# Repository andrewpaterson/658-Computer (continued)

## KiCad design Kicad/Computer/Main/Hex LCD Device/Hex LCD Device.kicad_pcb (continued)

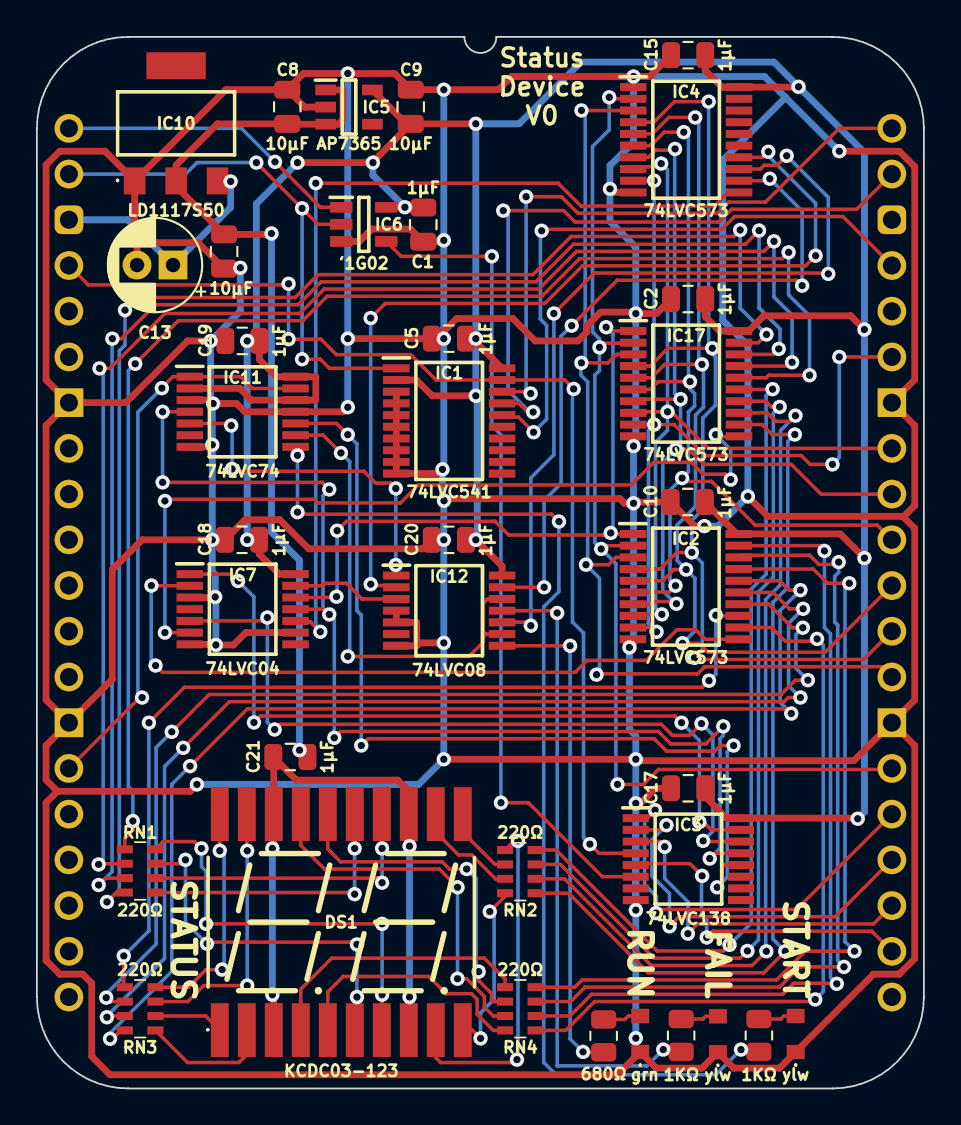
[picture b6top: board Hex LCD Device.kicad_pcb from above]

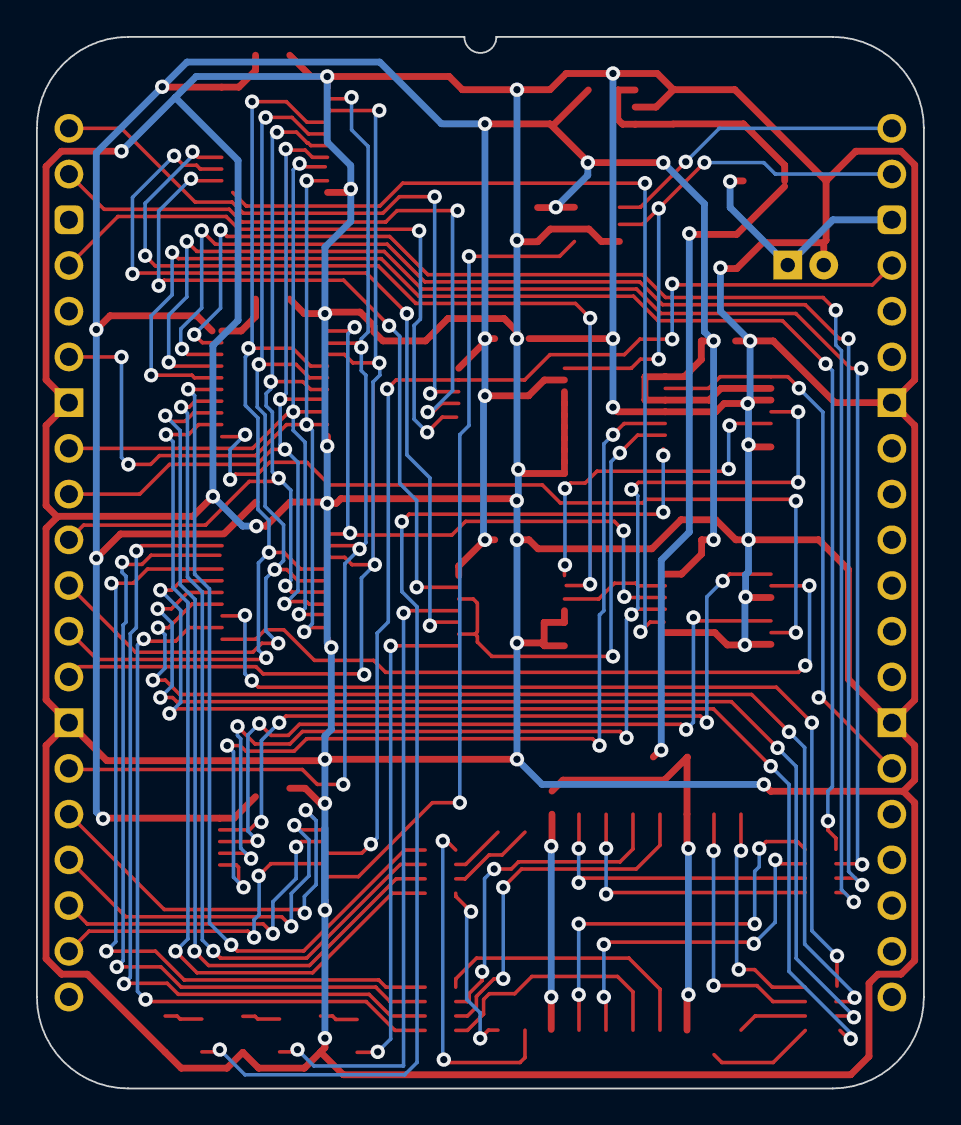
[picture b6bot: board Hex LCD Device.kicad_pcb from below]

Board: 2 copper layers, 49.3 x 58.4 mm, 40 parts (2 on the bottom side), 77 nets.

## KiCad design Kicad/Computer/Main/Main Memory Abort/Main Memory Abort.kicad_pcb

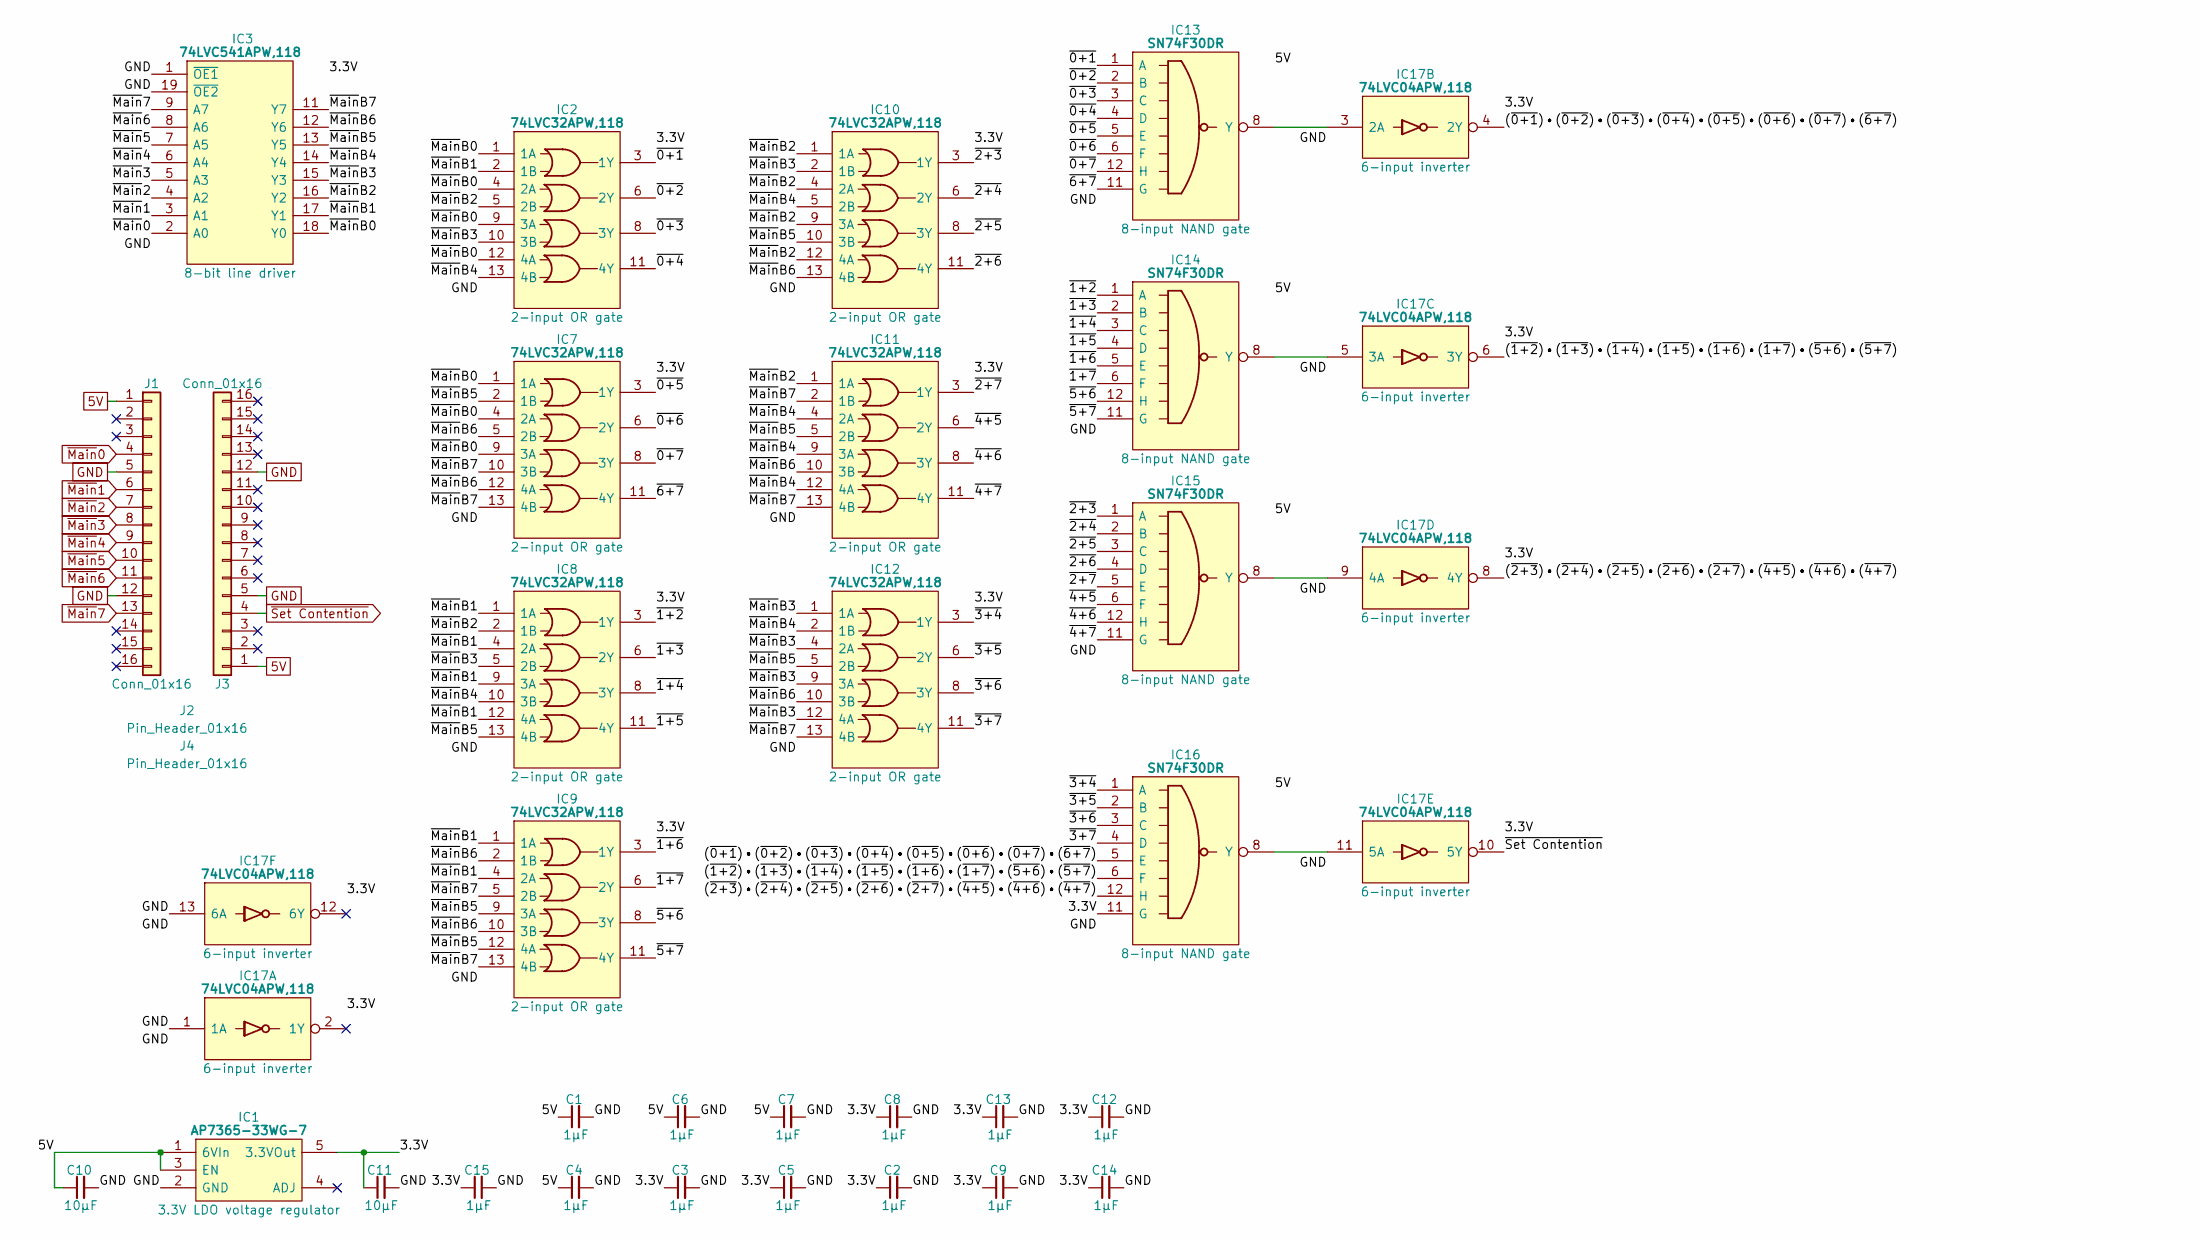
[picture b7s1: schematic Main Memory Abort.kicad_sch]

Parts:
C1, C2, C3, C4, C5, C6, C7, C8, C9, C12, C13, C14, C15: 1μF; C_0805
C10, C11: 10µF; C_0805
IC1: AP7365-33WG-7; SOT95P285X130-5N; Manufacturer_Part_Number AP7365-33WG-7; Mouser Part Number 621-AP7365-33WG-7
IC2, IC7, IC8, IC9, IC10, IC11, IC12: 74LVC32APW,118; SOP65P640X110-14N; Manufacturer_Part_Number 74LVC32APW,118; Mouser Part Number 771-74LVC32APW-T
IC3: 74LVC541APW,118; SOP65P640X110-20N; Mouser Part Number 771-74LVC541APW-T
IC13, IC14, IC15, IC16: SN74F30DR; SOIC127P600X175-14N; Manufacturer_Part_Number SN74F30DR; Mouser Part Number 595-SN74F30DR
IC17: 74LVC04APW,118; SOP65P640X110-14N; Manufacturer_Part_Number 74LVC04APW,118; Mouser Part Number 771-74LVC04APW-T
J1, J3: Conn_01x16; SIP_16_Pins
J2, J4: Pin_Header_01x16; PinHeader_1x16_P2.54mm_Vertical

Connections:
5V: C1.1, C4.1, C6.1, C7.1, C10.1, IC1.1 (6VIn), IC1.3 (EN), IC13.14 (5V), IC14.14 (5V), IC15.14 (5V), IC16.14 (5V), J1.1, J3.1
/3.3V: C2.1, C3.1, C5.1, C8.1, C9.1, C11.1, C12.1, C13.1, C14.1, C15.1, IC1.5 (3.3VOut), IC2.14 (3V), IC3.20 (3V), IC7.14 (3V), IC8.14 (3V), IC9.14 (3V), IC10.14 (3V), IC11.14 (3V), IC12.14 (3V), IC16.11 (G), IC17.14 (3V)
/(~0+1)•(~0+2)•(~0+3)•(~0+4)•(~0+5)•(~0+6)•(~0+7)•(~6+7): IC16.5 (E), IC17.4 (2Y)
/(~1+2)•(~1+3)•(~1+4)•(~1+5)•(~1+6)•(~1+7)•(~5+6)•(~5+7): IC16.6 (F), IC17.6 (3Y)
/(~2+3)•(~2+4)•(~2+5)•(~2+6)•(~2+7)•(~4+5)•(~4+6)•(~4+7): IC16.12 (H), IC17.8 (4Y)
/~0+1: IC2.3 (1Y), IC13.1 (A)
/~0+2: IC2.6 (2Y), IC13.2 (B)
/~0+3: IC2.8 (3Y), IC13.3 (C)
/~0+4: IC2.11 (4Y), IC13.4 (D)
/~0+5: IC7.3 (1Y), IC13.5 (E)
/~0+6: IC7.6 (2Y), IC13.6 (F)
/~0+7: IC7.8 (3Y), IC13.12 (H)
/~1+2: IC8.3 (1Y), IC14.1 (A)
/~1+3: IC8.6 (2Y), IC14.2 (B)
/~1+4: IC8.8 (3Y), IC14.3 (C)
/~1+5: IC8.11 (4Y), IC14.4 (D)
/~1+6: IC9.3 (1Y), IC14.5 (E)
/~1+7: IC9.6 (2Y), IC14.6 (F)
/~2+3: IC10.3 (1Y), IC15.1 (A)
/~2+4: IC10.6 (2Y), IC15.2 (B)
/~2+5: IC10.8 (3Y), IC15.3 (C)
/~2+6: IC10.11 (4Y), IC15.4 (D)
/~2+7: IC11.3 (1Y), IC15.5 (E)
/~3+4: IC12.3 (1Y), IC16.1 (A)
/~3+5: IC12.6 (2Y), IC16.2 (B)
/~3+6: IC12.8 (3Y), IC16.3 (C)
/~3+7: IC12.11 (4Y), IC16.4 (D)
/~4+5: IC11.6 (2Y), IC15.6 (F)
/~4+6: IC11.8 (3Y), IC15.12 (H)
/~4+7: IC11.11 (4Y), IC15.11 (G)
/~5+6: IC9.8 (3Y), IC14.12 (H)
/~5+7: IC9.11 (4Y), IC14.11 (G)
/~6+7: IC7.11 (4Y), IC13.11 (G)
/~MainB0: IC2.1 (1A), IC2.4 (2A), IC2.9 (3A), IC2.12 (4A), IC3.18 (Y0), IC7.1 (1A), IC7.4 (2A), IC7.9 (3A)
/~MainB1: IC2.2 (1B), IC3.17 (Y1), IC8.1 (1A), IC8.4 (2A), IC8.9 (3A), IC8.12 (4A), IC9.1 (1A), IC9.4 (2A)
/~MainB2: IC2.5 (2B), IC3.16 (Y2), IC8.2 (1B), IC10.1 (1A), IC10.4 (2A), IC10.9 (3A), IC10.12 (4A), IC11.1 (1A)
/~MainB3: IC2.10 (3B), IC3.15 (Y3), IC8.5 (2B), IC10.2 (1B), IC12.1 (1A), IC12.4 (2A), IC12.9 (3A), IC12.12 (4A)
/~MainB4: IC2.13 (4B), IC3.14 (Y4), IC8.10 (3B), IC10.5 (2B), IC11.4 (2A), IC11.9 (3A), IC11.12 (4A), IC12.2 (1B)
/~MainB5: IC3.13 (Y5), IC7.2 (1B), IC8.13 (4B), IC9.9 (3A), IC9.12 (4A), IC10.10 (3B), IC11.5 (2B), IC12.5 (2B)
/~MainB6: IC3.12 (Y6), IC7.5 (2B), IC7.12 (4A), IC9.2 (1B), IC9.10 (3B), IC10.13 (4B), IC11.10 (3B), IC12.10 (3B)
/~MainB7: IC3.11 (Y7), IC7.10 (3B), IC7.13 (4B), IC9.5 (2B), IC9.13 (4B), IC11.2 (1B), IC11.13 (4B), IC12.13 (4B)
GND: C1.2, C2.2, C3.2, C4.2, C5.2, C6.2, C7.2, C8.2, C9.2, C10.2, C11.2, C12.2, C13.2, C14.2, C15.2, IC1.2 (GND), IC2.7 (GND), IC3.1 (~OE1), IC3.10 (GND), IC3.19 (~OE2), IC7.7 (GND), IC8.7 (GND), IC9.7 (GND), IC10.7 (GND), IC11.7 (GND), IC12.7 (GND), IC13.7 (GND), IC14.7 (GND), IC15.7 (GND), IC16.7 (GND), IC17.1 (1A), IC17.7 (GND), IC17.13 (6A), J1.5, J1.12, J3.5, J3.12
unnamed: IC13.8 (Y), IC17.3 (2A)
unnamed: IC14.8 (Y), IC17.5 (3A)
unnamed: IC15.8 (Y), IC17.9 (4A)
unnamed: IC16.8 (Y), IC17.11 (5A)
~Main0: IC3.2 (A0), J1.4
~Main1: IC3.3 (A1), J1.6
~Main2: IC3.4 (A2), J1.7
~Main3: IC3.5 (A3), J1.8
~Main4: IC3.6 (A4), J1.9
~Main5: IC3.7 (A5), J1.10
~Main6: IC3.8 (A6), J1.11
~Main7: IC3.9 (A7), J1.13
~Set Contention: IC17.10 (5Y), J3.4

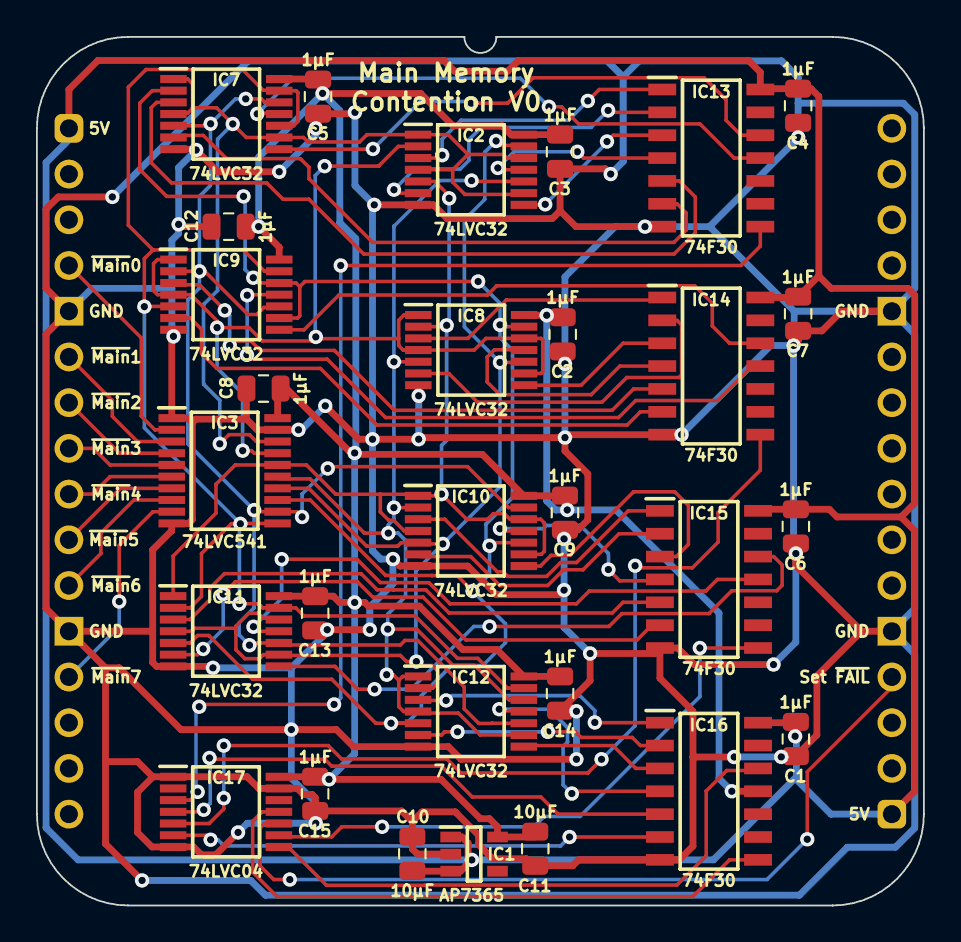
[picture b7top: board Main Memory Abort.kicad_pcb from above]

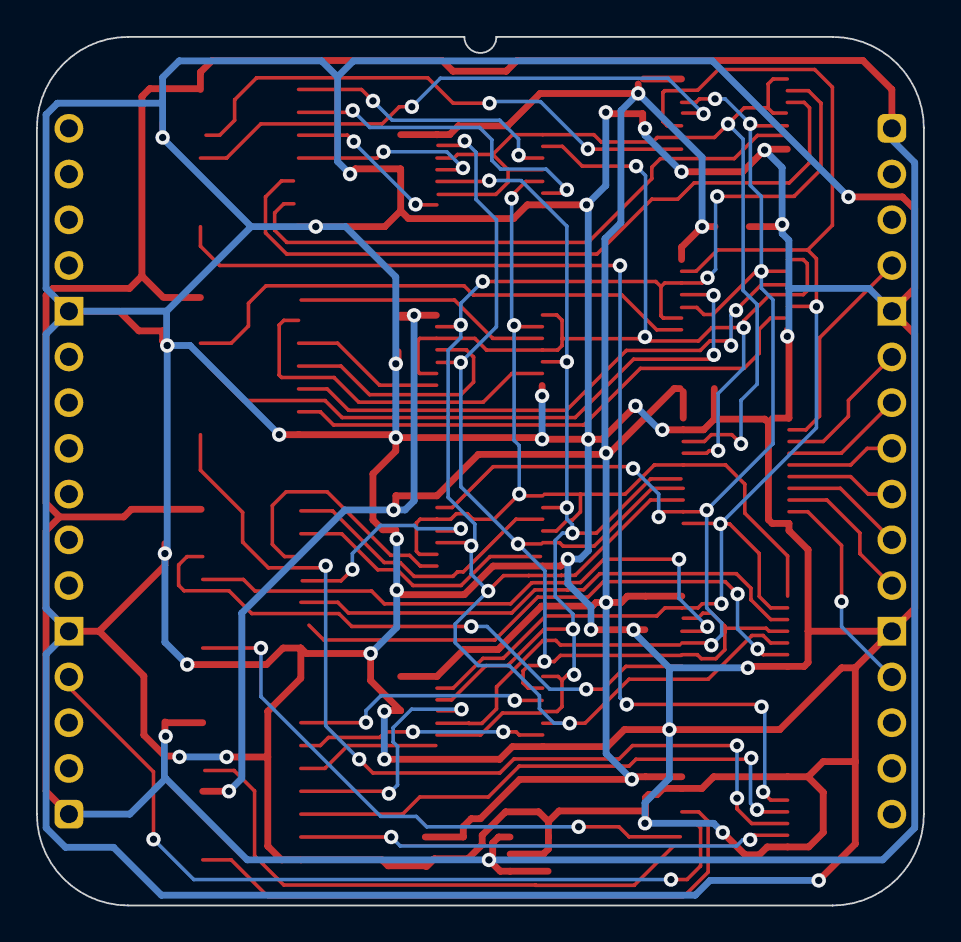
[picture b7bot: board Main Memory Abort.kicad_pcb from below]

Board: 2 copper layers, 49.3 x 48.3 mm, 33 parts (2 on the bottom side), 55 nets.

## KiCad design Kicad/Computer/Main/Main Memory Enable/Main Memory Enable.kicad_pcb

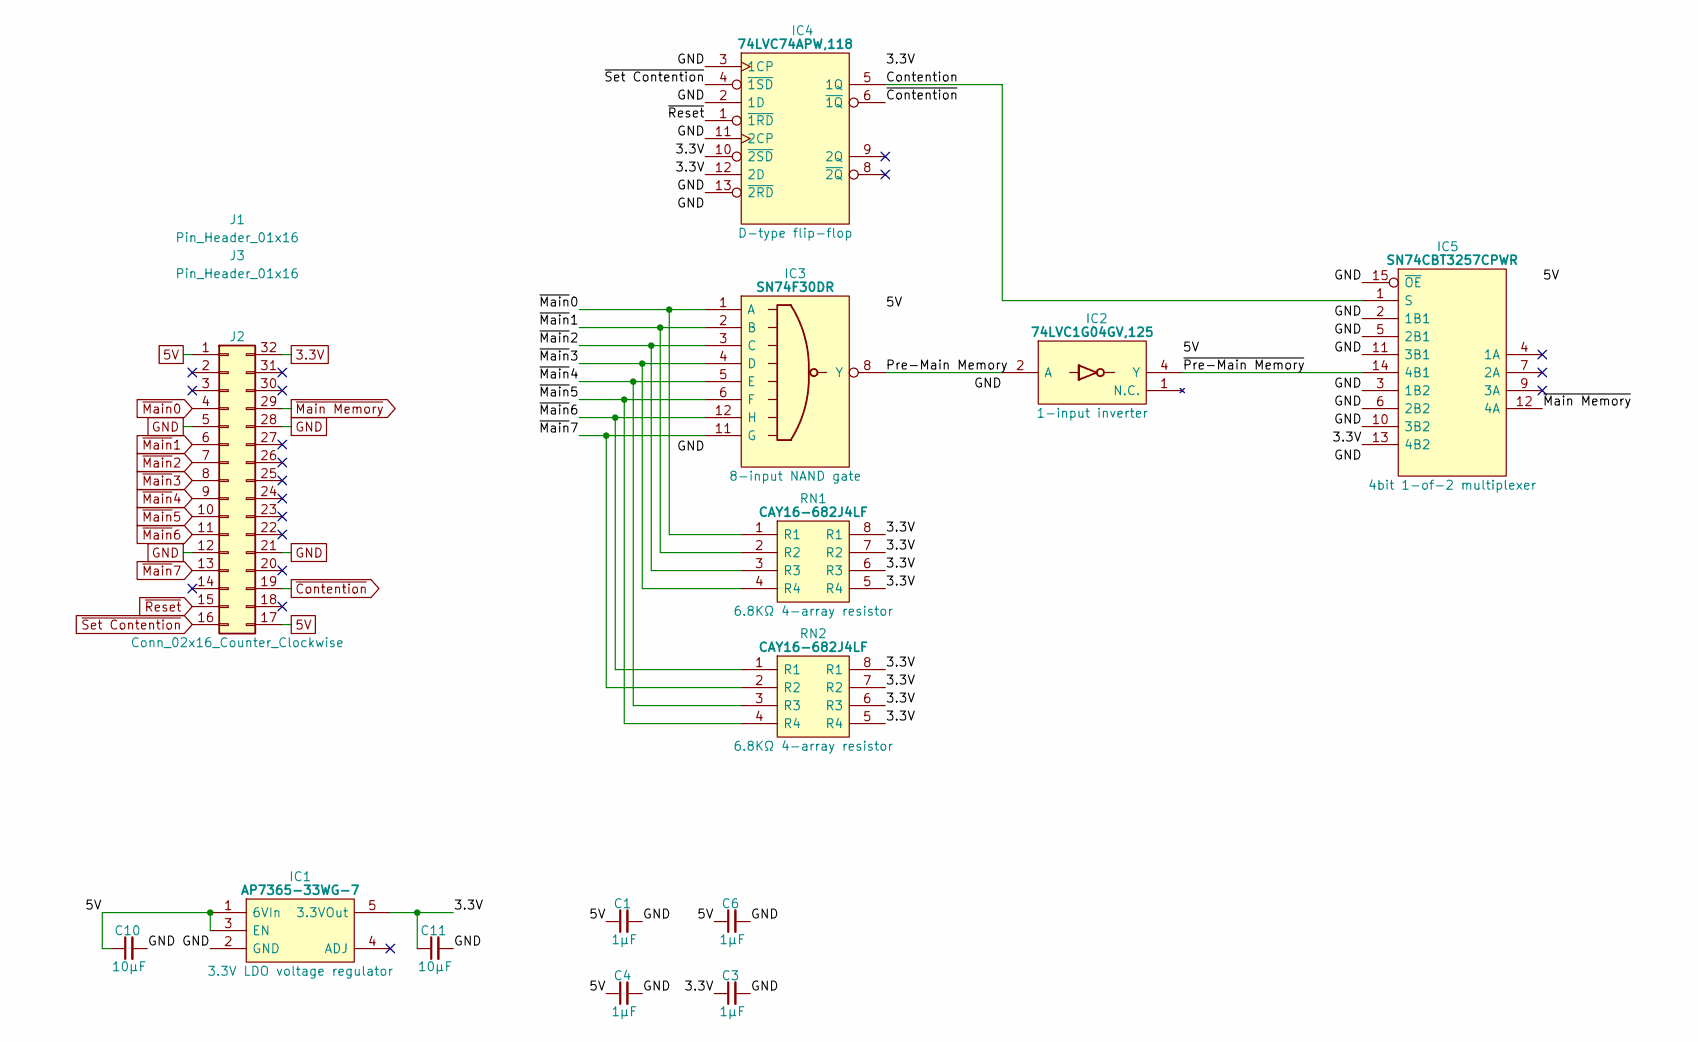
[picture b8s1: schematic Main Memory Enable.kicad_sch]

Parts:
C1, C3, C4, C6: 1μF; C_0805
C10, C11: 10µF; C_0805
IC1: AP7365-33WG-7; SOT95P285X130-5N; Manufacturer_Part_Number AP7365-33WG-7; Mouser Part Number 621-AP7365-33WG-7
IC2: 74LVC1G04GV,125; SOT95P275X110-5N; Manufacturer_Part_Number 74LVC1G04GV,125; Mouser Part Number 771-74LVC1G04GV
IC3: SN74F30DR; SOIC127P600X175-14N; Manufacturer_Part_Number SN74F30DR; Mouser Part Number 595-SN74F30DR
IC4: 74LVC74APW,118; SOP65P640X110-14N; Mouser Part Number 771-74LVC74APW-T
IC5: SN74CBT3257CPWR; SOP65P640X120-16N; Manufacturer_Part_Number SN74CBT3257CPWR; Mouser Part Number 595-SN74CBT3257CPWR
J1, J3: Pin_Header_01x16; PinHeader_1x16_P2.54mm_Vertical
J2: Conn_02x16_Counter_Clockwise; DIP-32_Board_W15.24mm
RN1, RN2: CAY16-682J4LF; CAY16-J4

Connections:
3.3V: C3.1, C11.1, IC1.5 (3.3VOut), IC4.10 (~2SD), IC4.12 (2D), IC4.14 (3V), IC5.13 (4B2), J2.32, RN1.5 (R4), RN1.6 (R3), RN1.7 (R2), RN1.8 (R1), RN2.5 (R4), RN2.6 (R3), RN2.7 (R2), RN2.8 (R1)
5V: C1.1, C4.1, C6.1, C10.1, IC1.1 (6VIn), IC1.3 (EN), IC2.5 (3V), IC3.14 (5V), IC5.16 (5V), J2.1, J2.17
/Contention: IC4.5 (1Q), IC5.1 (S)
/Pre-Main Memory: IC2.2 (A), IC3.8 (Y)
/~Pre-Main Memory: IC2.4 (Y), IC5.14 (4B1)
GND: C1.2, C3.2, C4.2, C6.2, C10.2, C11.2, IC1.2 (GND), IC2.3 (GND), IC3.7 (GND), IC4.2 (1D), IC4.3 (1CP), IC4.7 (GND), IC4.11 (2CP), IC4.13 (~2RD), IC5.2 (1B1), IC5.3 (1B2), IC5.5 (2B1), IC5.6 (2B2), IC5.8 (GND), IC5.10 (3B2), IC5.11 (3B1), IC5.15 (~OE), J2.5, J2.12, J2.21, J2.28
~Contention: IC4.6 (~1Q), J2.19
~Main Memory: IC5.12 (4A), J2.29
~Main0: IC3.1 (A), J2.4, RN1.1 (R1)
~Main1: IC3.2 (B), J2.6, RN1.2 (R2)
~Main2: IC3.3 (C), J2.7, RN1.3 (R3)
~Main3: IC3.4 (D), J2.8, RN1.4 (R4)
~Main4: IC3.5 (E), J2.9, RN2.3 (R3)
~Main5: IC3.6 (F), J2.10, RN2.4 (R4)
~Main6: IC3.12 (H), J2.11, RN2.1 (R1)
~Main7: IC3.11 (G), J2.13, RN2.2 (R2)
~Reset: IC4.1 (~1RD), J2.15
~Set Contention: IC4.4 (~1SD), J2.16

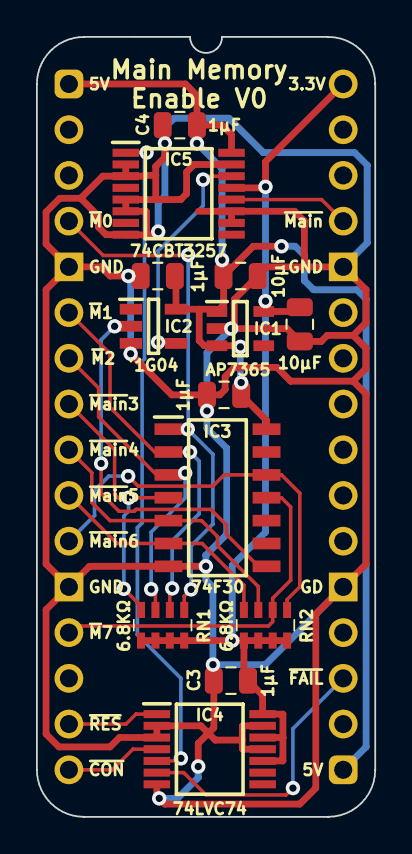
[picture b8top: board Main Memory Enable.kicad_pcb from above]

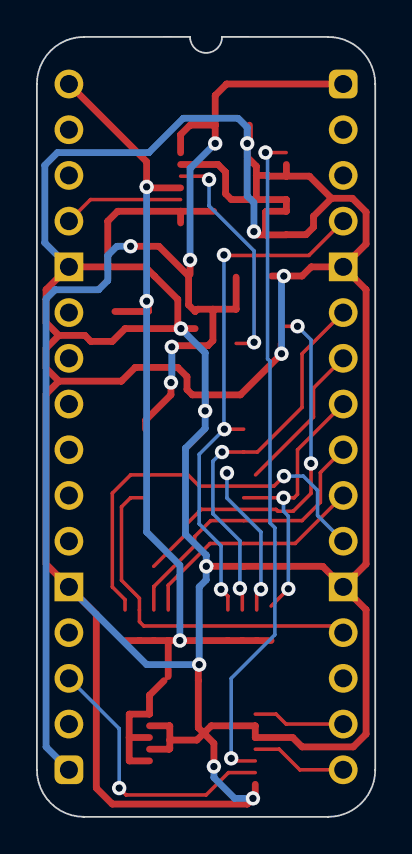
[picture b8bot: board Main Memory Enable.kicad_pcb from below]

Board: 2 copper layers, 18.8 x 43.3 mm, 16 parts (2 on the bottom side), 18 nets.
